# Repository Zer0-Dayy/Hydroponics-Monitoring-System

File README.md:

# Hydroponics Monitoring System

An ESP32-S3 controller monitors a hydroponic reservoir and its surroundings,
makes local grow-lamp and alarm decisions, and sends readings to a Windows or
Linux desktop app over Bluetooth Low Energy (BLE). The app handles sensor
setup, calibration, diagnostics, and history export. The custom PCB is
designed to keep the controller and selected sensors powered from a 3S
battery when external 5 V is lost.

## Start here

| If you want to… | Start with… |
| --- | --- |
| Explore without a board | [Install the desktop app](BluetoothControlApp/Readme.md#install-and-run) and [walk through the simulator](BluetoothControlApp/Readme.md#walk-through-the-demo). |
| Review or manufacture the PCB | Open the [Rev 1.5 PCB guide](PCB%20Design/README.md) for the schematic, connector pinout, power paths, BOM, and fabrication checks. |
| Build or flash firmware | [Build with PlatformIO](Firmware/README.md#build-and-test) and follow the [bench bring-up](Firmware/README.md#bench-bring-up). |
| Commission a controller | [Connect over BLE](BluetoothControlApp/Readme.md#connect-to-a-controller), then check sensor health, calibrate the probes, and export a sample history. |
| Work on the app or protocol | See the [app development guide](BluetoothControlApp/Readme.md#develop-and-test) and the [BLE v2 contract](BluetoothControlApp/FirmwareContract.md). |

## How it fits together

```mermaid
flowchart LR
    Sensors["Seven sensor modules"] --> Controller["ESP32-S3 and FreeRTOS"]
    Controller --> Relay["Grow-lamp relay control"]
    Controller <-->|BLE v2| App["Hydroponics Control desktop app"]
    App --> History["Local SQLite history"]
    Controller -->|Optional Wi-Fi| Network["Access point"]
```

The PCB routes I²C, 1-Wire, analog inputs, and ultrasonic timing signals
to the ESP32-S3. The firmware schedules measurements and publishes a
snapshot with units, sample age, and health. A separate Safety task owns
the relay, so local control continues independently of the desktop
connection. The controller stores sensor settings and calibration in
flash. The app keeps a separate copy of the readings it receives.

BLE carries live State, Telemetry, alarms, and commissioning commands.
The Wi-Fi page configures the controller's own network connection. MQTT
publishing and a remote dashboard appear in the redesign documents as
planned work. The current system uses the BLE desktop app and local
history.

## What it measures

| Sensor | Measurements | Power branch |
| --- | --- | --- |
| BME280 | Air temperature (°C), relative humidity (% RH), and pressure (Pa) | Retained 3.3 V |
| DS18B20 | Water temperature (°C) | Retained 3.3 V |
| DFR0026 | Light signal (mV), or illuminance (lux) after reference calibration | Retained 3.3 V |
| SGP30 | Total volatile organic compounds (ppb) and estimated CO₂ equivalent (ppm) | Retained 3.3 V |
| HC-SR04 | Distance to the water surface (mm) | External 5 V |
| pH-4502C | Reservoir pH | External 5 V |
| SEN0244 | Temperature-compensated total dissolved solids (ppm) | External 5 V |

The relay interface also uses external 5 V. Firmware 0.11.0 reports the
external power state by default. The optional power handover stops 5 V
sensing and pauses Wi-Fi on rail loss. That mode still needs validation
on the assembled board. The BLE link is open and carries Wi-Fi
credentials unencrypted. [Firmware power policy](Firmware/README.md#power-and-safety-policy) · [BLE link details](BluetoothControlApp/FirmwareContract.md#bluetooth-le)

## Design references and project history

- The October redesign defines the system requirements and validation
  plan. The SysML package maps requirements to components, interfaces,
  and test cases. [Redesign specification, Rev 5](Documentation/Redesign%20Specification.pdf) · [SysML diagrams](Documentation/SysML%20Diagrams.pdf)
- The firmware architecture records module boundaries and design
  decisions. Its RTOS companion explains tasks, scheduling, and
  supervision. The guided textbook walks through a snapshot of the
  implementation. [Firmware architecture](Firmware/Firmware%20Architecture.pdf) · [RTOS architecture](Firmware/RTOS%20Architecture.pdf) · [Guided firmware textbook](Documentation/Hydroponics%20Firmware.pdf)
- The dated bench notes preserve the earlier development-board and
  breadboard results. Use the Rev 1.5 schematic and connector guide when
  wiring the custom PCB. [Bench notes](Firmware/docs/bench-notes.md) · [PCB guide](PCB%20Design/README.md)
- The original handover documents the earlier ESP32, EdgeX, and MQTT
  prototype. The provenance document records the current firmware and app
  source, attribution, and license scope. [Original handover](Project%20Handover/Source%20Code/HANDOVER.md) · [Provenance](PROVENANCE.md)

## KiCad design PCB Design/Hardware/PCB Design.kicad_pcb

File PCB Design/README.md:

# Hydroponics Monitoring System · PCB revision 1.8

Open **Hardware/PCB Design.kicad_pro** in KiCad 10. The fabrication plots, assembly exports and rule checks were regenerated using **KiCad 10.0.8**. Install the standard KiCad 10 symbol libraries and the optional KiCad 10 3D model library to view the packaged model references.
 
See **Documentation/Port And LED Map.pdf** for the USB, UART and indicator locations. **BOM/Instructions Atelier.md** defines the factory assembly.

## Manufacturing handoff

| Directory | Contents |
| --- | --- |
| Hardware | Editable KiCad project, schematic, board, local symbols, footprints and library tables. Open PCB Design.kicad_pro. |
| Fabrication | 2-layer Gerbers, both silkscreens, plated and non-plated drill files with G85 slots, Gerber job and IPC-D-356 electrical test netlist. |
| BOM | Assembly_BOM.csv gives the factory population status for every schematic item. Placement_Top_SMT.csv is the default SMT pick-and-place file. Positions_All_Design.csv is a coordinate reference for all 84 footprints. Sourcing_Notes.csv retains earlier candidate suppliers and adds the Rev 1.8 components. |
| Documentation | Schematic, 1:1 top assembly and mirrored back markings, front and back copper drawings viewed from above, and the connector and LED map. |
| Validation | KiCad 10 ERC and DRC reports, drill maps, and regeneration checks for connectivity, geometry and the assembly files. |

**Factory build**. Fit the J15/J16 1×5 female through-hole sockets, the J17 1×4 male header, J18 1×2 header with removable shorting shunt and all five LEDs. Fit both Micro-B receptacles and all three 0Ω links. The front stencil includes these five parts. Solder and inspect all four shell anchors on each receptacle. Leave J9, J10 and J12 empty for the owner’s modules. Supply both silkscreens. Maintain the original 165.5 × 90.5 mm outline, four M3 mounting positions, 1.5 mm FR-4 and 35 µm copper per side. Review plated shell slots and the four new non-plated standoff slots with the fabricator.

## USB service options

| Function | Plug-in breakout | Factory-installed primary | If a port is damaged |
| --- | --- | --- | --- |
| Native data | J15. Pin 2 D−, pin 3 D+, pin 5 GND. Pins 1 and 4 isolated. | Fit a mechanically matched J1 and both 0Ω links R25/R26. | Disconnect power. Remove both links to isolate the direct D lines. Inspect the footprint for shorts to power or ground before installing a supported J15 breakout. |
| External 5V | J16. Pin 1 VBUS and pin 5 GND. Pins 2–4 isolated. | Fit a mechanically matched J3 and R27. Use a jumper rated ≥1.5A. | Disconnect power. Remove R27 to isolate J3 VBUS. Inspect for shorts and supply 5V through J16. |
| ROM recovery | J17. Pin 1 GND, pin 2 PCB TX, pin 3 PCB RX, pin 4 ESP_3V3. | 3.3V USB-to-UART adapter with crossed TX/RX and either board power (J18 closed, pin 4 free) or ESP-only power (J18 open). | The ROM can return its MAC address over UART even when the native USB path is unusable. |

Use a single host for native data and a single source for EXT_5V. With power off, desolder the indicated 0Ω component(s) and leave their copper pads intact. Verify isolation before attaching the replacement breakout. The J15 carrier and J1 occupy a common plug-access area. For a different carrier shape, secure the carrier to the enclosure and use a short pin-mapped harness. The unknown generic loose receptacle has no verified land pattern. Check the proposed part against the Amphenol footprint before assembly; flag a mismatch before fitting a substitute.

## Field connector pinout

| Ref | Terminals in numerical order | ESP32-S3 signal |
| --- | --- | --- |
| J2 · BME280 and J11 · SGP30 | SDA, SCL, GND, 3.3V | GPIO21 SDA, GPIO47 SCL |
| J4 · DS18B20 | GND, 3.3V, DQ | GPIO14 |
| J5 · SEN0244 | GND, EXT_5V, AOUT | GPIO6 |
| J7 · HC-SR04 | EXT_5V, TRIG, ECHO, GND | GPIO17 trigger, GPIO18 divided echo |
| J8 · DFR0026 | Signal, 3.3V, GND | GPIO1 |
| J13 · Relay | EXT_5V, relay control, GND | GPIO15 |
| J14 · pH-4502C | EXT_5V, GND, GND, PO | GPIO7 through divider |

J6 accepts battery positive on pin 1 and ground on pin 2. J9 produces BAT_5V. The common diode cathodes feed J12 at SYS_IN. External-rail sensing remains on GPIO8 through 10kΩ over 13.6kΩ. J5 pin 2 now reads EXT_5V in its schematic symbol. Its electrical connection is the same as Rev 1.5.

## Bench evidence

At first power-up, measure the rails to ground. D3 indicates EXT_5V, D4 indicates BAT_5V, D5 indicates SYS_IN after the isolation diodes, and D6 indicates the ESP supply at U1. D7 is active high on GPIO9 and requires firmware that toggles that output. EN should return high after reset. Enter the ROM loader for the read-only MAC test, then run a GPIO9 heartbeat application on a test board if desired. A toggling GPIO9 proves the diagnostic task is running. Qualify the sensor channels, UPS handover, USB connection under cable movement and loaded rails on a physical first article.

To repeat the CAD checks from the Hardware directory:

```sh
kicad-cli sch erc --exit-code-violations -o erc.rpt 'PCB Design.kicad_sch'
kicad-cli pcb drc --all-track-errors --schematic-parity --exit-code-violations -o drc.rpt 'PCB Design.kicad_pcb'
```

## ESP-only programming

With all power off, remove the J18 shunt and disconnect external 5V, battery, charger and sensor/relay cables. Feed regulated 3.3V rated for at least 500mA into J17 pin 4 with common ground on pin 1. Use 3.3V UART logic. Use a separate 3.3V supply if the adapter cannot supply that current. After flashing, disconnect programmer power before reinstalling the J18 shunt for normal operation. D6 indicates the local ESP rail. Before plugging in sensors, verify that J12 OUT+ and J2 pin 4 remain near 0V in this mode. Peripheral GPIOs can feed unpowered devices through their protection diodes.

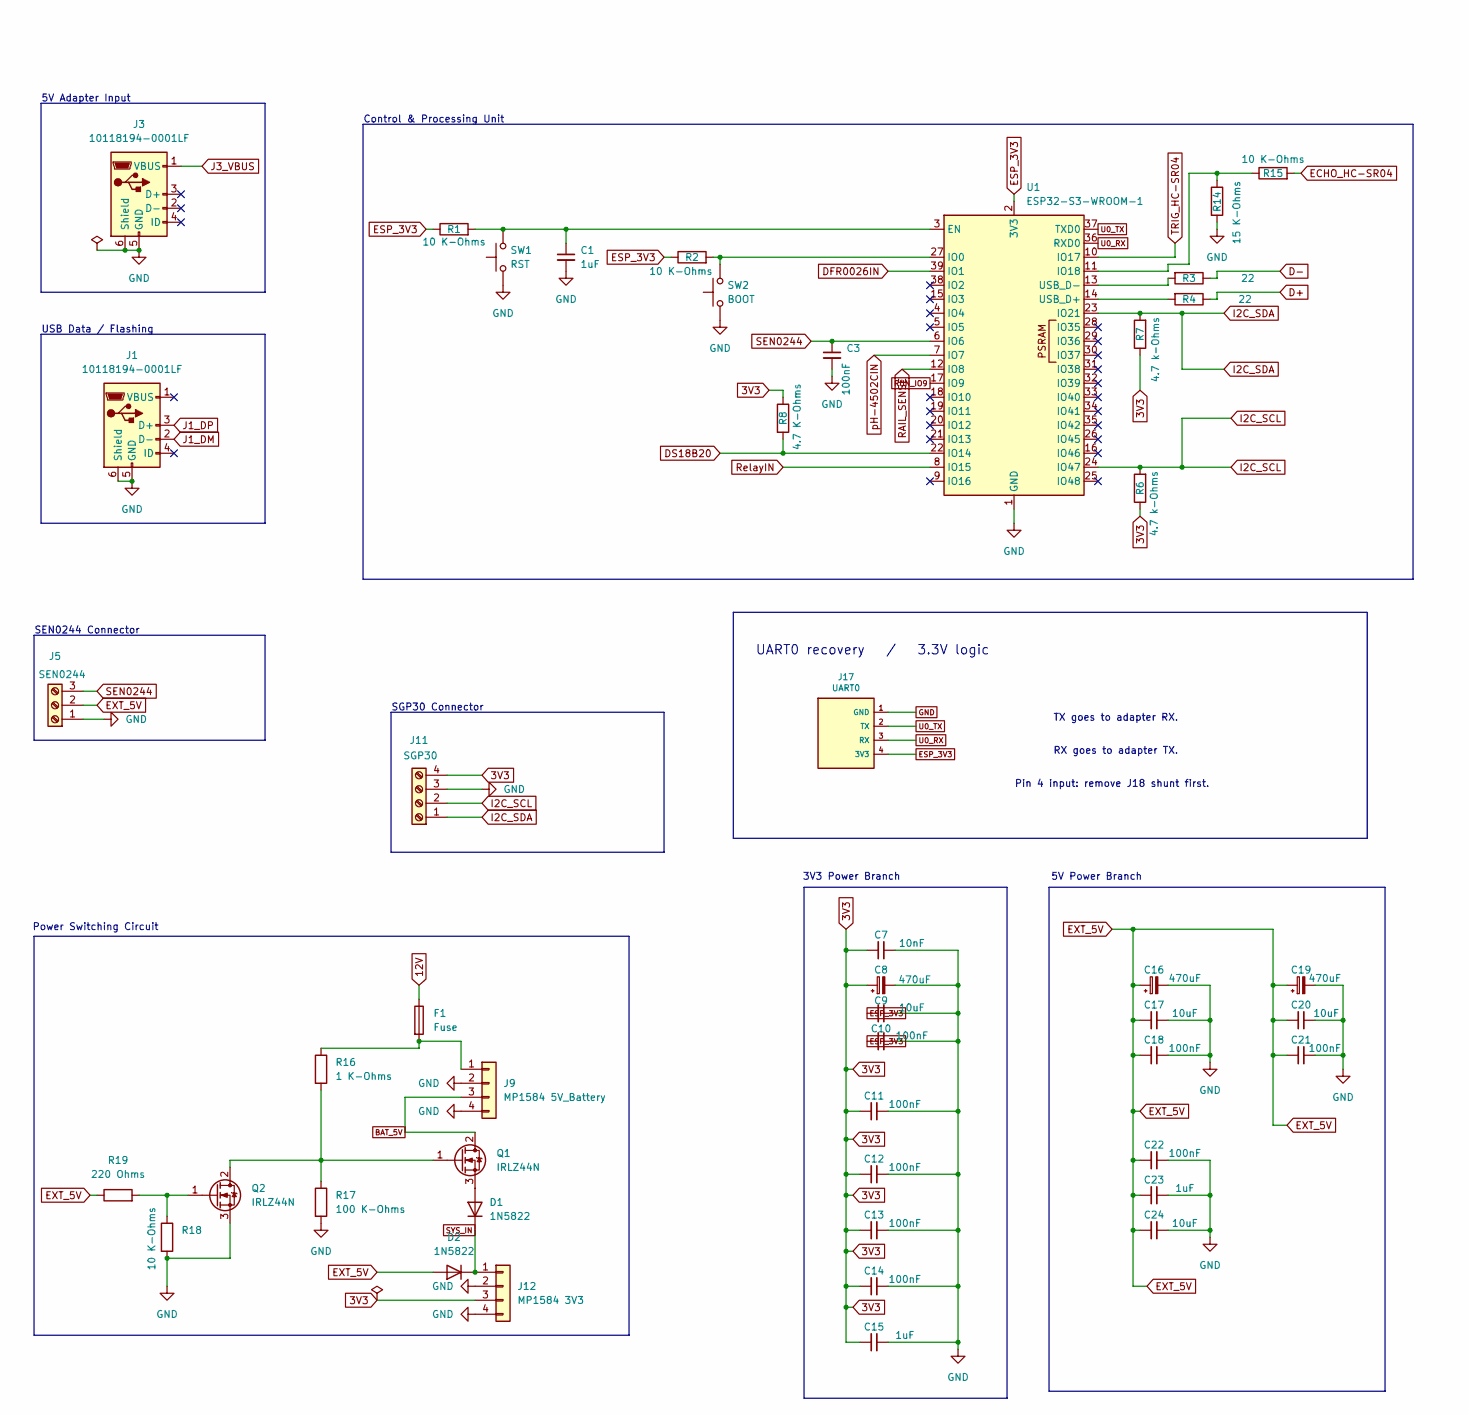
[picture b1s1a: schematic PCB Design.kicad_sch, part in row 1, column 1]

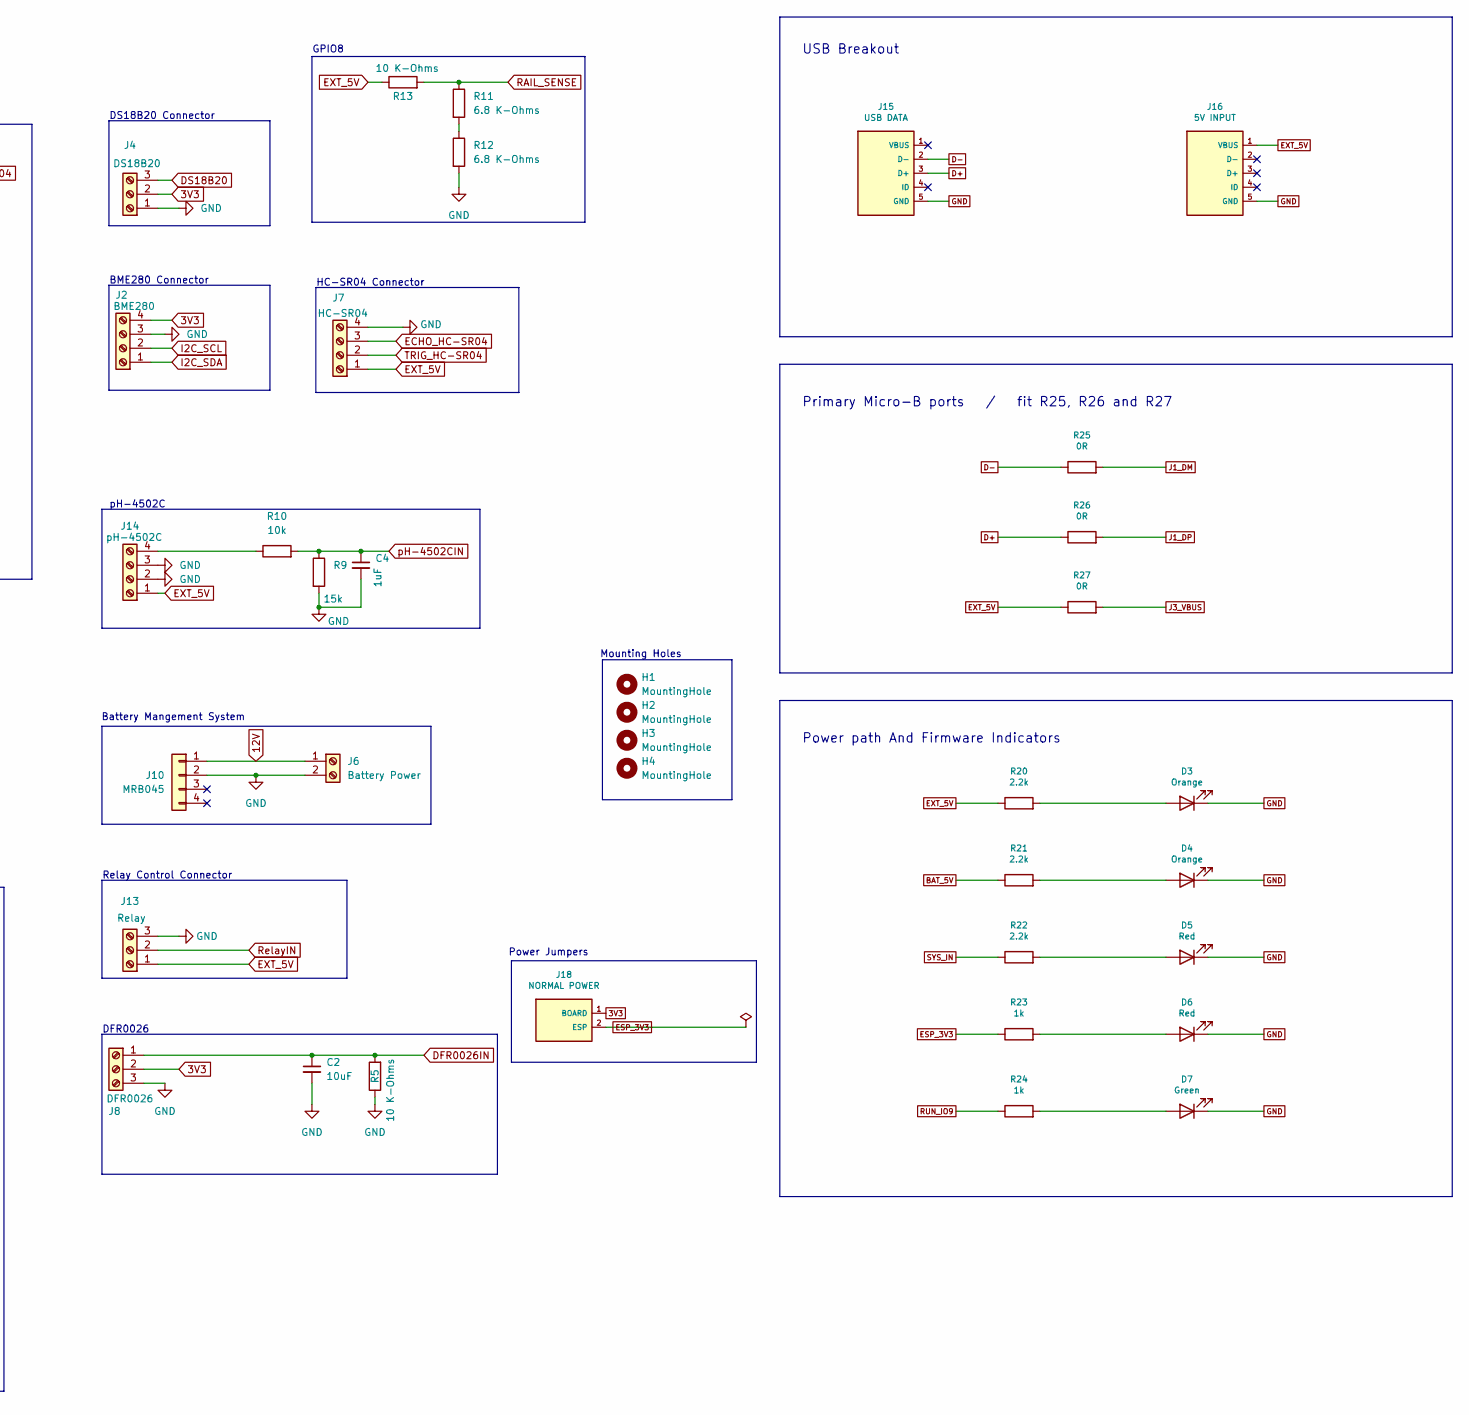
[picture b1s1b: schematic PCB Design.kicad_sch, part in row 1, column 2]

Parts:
C1: 1uF; C_0402_1005Metric__C1
C2: 10uF; C_0805_2012Metric__C2
C3: 100nF; C_0805_2012Metric_Pad1.18x1.45mm_HandSolder__C3
C4: 1uF; C_0402_1005Metric__C4
C7: 10nF; C_0805_2012Metric__C7
C8: 470uF; CP_Radial_D5.0mm_P2.00mm__C8
C9: 10uF; C_0805_2012Metric__C9
C10: 100nF; C_0805_2012Metric__C10
C11: 100nF; C_0805_2012Metric__C11
C12: 100nF; C_0805_2012Metric__C12
C13: 100nF; C_0805_2012Metric__C13
C14: 100nF; C_0805_2012Metric__C14
C15: 1uF; C_0402_1005Metric__C15
C16: 470uF; CP_Radial_D5.0mm_P2.00mm__C16
C17: 10uF; C_0805_2012Metric__C17
C18: 100nF; C_0805_2012Metric__C18
C19: 470uF; CP_Radial_D5.0mm_P2.00mm__C19
C20: 10uF; C_0805_2012Metric__C20
C21: 100nF; C_0805_2012Metric__C21
C22: 100nF; C_0805_2012Metric__C22
C23: 1uF; C_0402_1005Metric__C23
C24: 10uF; C_0805_2012Metric__C24
D1: 1N5822; D_DO-201AD_P15.24mm_Horizontal__D1
D2: 1N5822; D_DO-201AD_P15.24mm_Horizontal__D2
D3, D4: Orange; LED_1206_3216Metric
D5, D6: Red; LED_1206_3216Metric
D7: Green; LED_1206_3216Metric
F1: Fuse; Fuse_Littelfuse_395Series__F1
H1: MountingHole; MountingHole_3.2mm_M3__H1
H2: MountingHole; MountingHole_3.2mm_M3__H2
H3: MountingHole; MountingHole_3.2mm_M3__H3
H4: MountingHole; MountingHole_3.2mm_M3__H4
J1, J3: 10118194-0001LF; USB_Micro-B_Amphenol_10118194-0001LF_Horizontal
J2: BME280; TerminalBlock_Phoenix_MKDS-1,5-4-5.08_1x04_P5.08mm_Horizont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
J4: DS18B20; TerminalBlock_Phoenix_MKDS-1,5-3-5.08_1x03_P5.08mm_Horizont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
J5: SEN0244; TerminalBlock_Phoenix_MKDS-1,5-3-5.08_1x03_P5.08mm_Horizont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
J6: Battery Power; TerminalBlock_Phoenix_MKDS-1,5-2-5.08_1x02_P5.08mm_Horizont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
J7: HC-SR04; TerminalBlock_Phoenix_MKDS-1,5-4-5.08_1x04_P5.08mm_Horizont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
J8: DFR0026; TerminalBlock_Phoenix_MKDS-1,5-3-5.08_1x03_P5.08mm_Horizont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
J9: MP1584 5V_Battery; MP1584EN_Module__J9
J10: MRB045; Charger_3S_TypeC_MRB045__J10
J11: SGP30; TerminalBlock_Phoenix_MKDS-1,5-4-5.08_1x04_P5.08mm_Horizont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
J12: MP1584 3V3; MP1584EN_Module__J12
J13: Relay; TerminalBlock_Phoenix_MKDS-1,5-3-5.08_1x03_P5.08mm_Horizont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
J14: pH-4502C; TerminalBlock_Phoenix_MKDS-1,5-4-5.08_1x04_P5.08mm_Horizont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
J15: USB DATA; USB_Breakout_1x05_M2
J16: 5V INPUT; USB_Breakout_1x05_M2
J17: UART0; PinHeader_1x04_P2.54mm_Vertical
J18: NORMAL POWER; PinHeader_1x02_P2.54mm_Vertical
Q1: IRLZ44N; TO-220-3_Vertical__Q1
Q2: IRLZ44N; TO-220-3_Vertical__Q2
R1: 10 K-Ohms; R_0603_1608Metric__R1
R2: 10 K-Ohms; R_0603_1608Metric__R2
R3: 22; R_0603_1608Metric__R3
R4: 22; R_0603_1608Metric__R4
R5: 10 K-Ohms; R_0603_1608Metric__R5
R6: 4.7 k-Ohms; R_0603_1608Metric__R6
R7: 4.7 k-Ohms; R_0603_1608Metric__R7
R8: 4.7 K-Ohms; R_0603_1608Metric__R8
R9: 15k; R_0603_1608Metric__R9
R10: 10k; R_0603_1608Metric__R10
R11: 6.8 K-Ohms; R_0603_1608Metric__R11; Tolerance 1%
R12: 6.8 K-Ohms; R_0603_1608Metric__R12; Tolerance 1%
R13: 10 K-Ohms; R_0603_1608Metric__R13; Tolerance 1%
R14: 15 K-Ohms; R_0603_1608Metric__R14; Tolerance 1%
R15: 10 K-Ohms; R_0603_1608Metric__R15; Tolerance 1%
R16: 1 K-Ohms; R_1206_3216Metric__R16
R17: 100 K-Ohms; R_0603_1608Metric__R17
R18: 10 K-Ohms; R_0603_1608Metric__R18
R19: 220 Ohms; R_0603_1608Metric__R19
R20, R21, R22: 2.2k; R_1206_3216Metric
R23, R24: 1k; R_1206_3216Metric
R25, R26: 0R; R_0603_1608Metric
R27: 0R; R_1206_3216Metric_HandLink
SW1: RST; SW_PUSH_6mm_H7.3mm__SW1
SW2: BOOT; SW_PUSH_6mm_H7.3mm__SW2
U1: ESP32-S3-WROOM-1; ESP32-S3-WROOM-1__U1

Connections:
3V3: C7.1, C8.1, C11.1, C12.1, C13.1, C14.1, C15.1, J2.4 (3V3), J4.2 (3V3), J8.2 (3V3), J11.4 (3V3), J12.3 (OUT+), J18.1 (BOARD), R6.1, R7.1, R8.1
12V: F1.1, J6.1, J10.1 (BAT+)
BAT_5V: J9.3 (OUT+), Q1.2 (D), R21.1
D+: J15.3 (D+), R4.1, R26.1
D-: J15.2 (D-), R3.1, R25.1
DFR0026IN: C2.1, J8.1 (SIGNAL), R5.2, U1.39 (IO1)
DS18B20: J4.3 (DQ), R8.2, U1.22 (IO14)
ECHO_HC-SR04: J7.3 (ECHO), R15.2
ESP_3V3: C9.1, C10.1, J17.4 (3V3), J18.2 (ESP), R1.1, R2.1, R23.1, U1.2 (3V3)
EXT_5V: C16.1, C17.1, C18.1, C19.1, C20.1, C21.1, C22.1, C23.1, C24.1, D2.2 (A), J5.2 (EXT_5V), J7.1 (5V), J13.1 (EXT_5V), J14.1 (EXT_5V), J16.1 (VBUS), R13.1, R19.1, R20.1, R27.1
GND: C1.2, C2.2, C3.2, C4.2, C7.2, C8.2, C9.2, C10.2, C11.2, C12.2, C13.2, C14.2, C15.2, C16.2, C17.2, C18.2, C19.2, C20.2, C21.2, C22.2, C23.2, C24.2, D3.1 (K), D4.1 (K), D5.1 (K), D6.1 (K), D7.1 (K), J1.5 (GND), J1.6 (Shield), J2.3 (GND), J3.5 (GND), J3.6 (Shield), J4.1 (GND), J5.1 (GND), J6.2, J7.4 (GND), J8.3 (GND), J9.2 (IN-), J9.4 (OUT-), J10.2 (BAT-), J11.3 (GND), J12.2 (IN-), J12.4 (OUT-), J13.3 (GND), J14.2 (GND), J14.3 (GND), J15.5 (GND), J16.5 (GND), J17.1 (GND), Q2.3 (S), R5.1, R9.2, R12.2, R14.2, R17.2, R18.2, SW1.1, SW2.1, U1.1 (GND), U1.40 (GND), U1.41 (GND)
I2C_SCL: J2.2 (SCL), J11.2 (SCL), R6.2, U1.24 (IO47)
I2C_SDA: J2.1 (SDA), J11.1 (SDA), R7.2, U1.23 (IO21)
J1_DM: J1.2 (D-), R25.2
J1_DP: J1.3 (D+), R26.2
J3_VBUS: J3.1 (VBUS), R27.2
unnamed: D1.2 (A), Q1.3 (S)
unnamed: D3.2 (A), R20.2
unnamed: D4.2 (A), R21.2
unnamed: D5.2 (A), R22.2
unnamed: D6.2 (A), R23.2
unnamed: D7.2 (A), R24.2
unnamed: F1.2, J9.1 (IN+), R16.1
unnamed: J14.4 (PO_ANALOG), R10.1
unnamed: Q1.1 (G), Q2.2 (D), R16.2, R17.1
unnamed: Q2.1 (G), R18.1, R19.2
unnamed: R11.2, R12.1
unnamed: C1.1, R1.2, SW1.2, U1.3 (EN)
unnamed: R2.2, SW2.2, U1.27 (IO0)
unnamed: R14.1, R15.1, U1.11 (IO18)
unnamed: R4.2, U1.14 (USB_D+)
unnamed: R3.2, U1.13 (USB_D-)
RAIL_SENSE: R11.1, R13.2, U1.12 (IO8)
RUN_IO9: R24.1, U1.17 (IO9)
RelayIN: J13.2 (RELAY_CTRL), U1.8 (IO15)
SEN0244: C3.1, J5.3 (AOUT), U1.6 (IO6)
SYS_IN: D1.1 (K), D2.1 (K), J12.1 (IN+), R22.1
TRIG_HC-SR04: J7.2 (TRIG), U1.10 (IO17)
U0_RX: J17.3 (RX), U1.36 (RXD0)
U0_TX: J17.2 (TX), U1.37 (TXD0)
pH-4502CIN: C4.1, R9.1, R10.2, U1.7 (IO7)

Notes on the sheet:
RX goes to adapter TX.
Control & Processing Unit
SEN0244 Connector
Primary Micro-B ports / fit R25, R26 and R27
USB Breakout
HC-SR04 Connector
3V3 Power Branch
SGP30 Connector
Power Switching Circuit
Power Jumpers
Mounting Holes
DFR0026
pH-4502C
BME280 Connector
UART0 recovery / 3.3V logic
Battery Mangement System
GPIO8
Pin 4 input: remove J18 shunt first.
Relay Control Connector
DS18B20 Connector
TX goes to adapter RX.
5V Power Branch
Power path And Firmware Indicators
USB Data / Flashing
5V Adapter Input

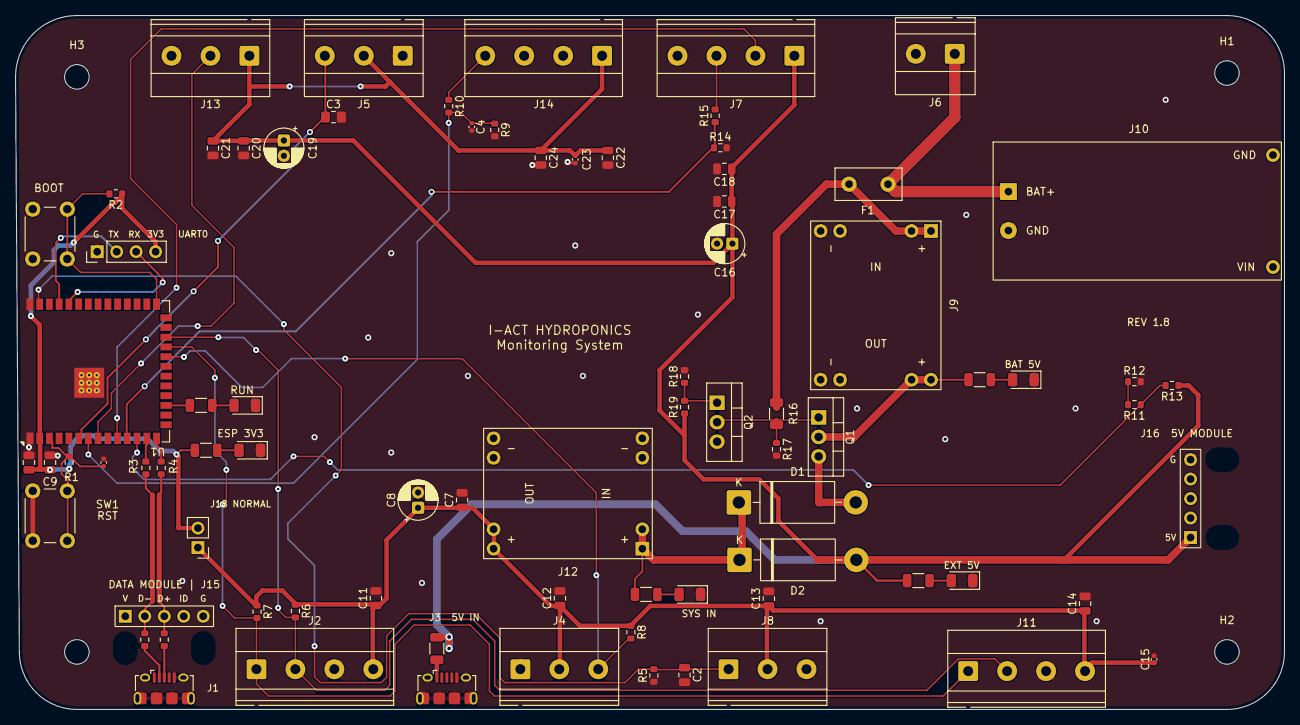
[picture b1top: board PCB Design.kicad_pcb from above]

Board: 2 copper layers, 165.5 x 90.5 mm, 84 parts (0 on the bottom side), 41 nets.

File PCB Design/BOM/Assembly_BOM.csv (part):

Ref,Quantity,Value,Footprint,Breakout build,Assembly note
C1,1,1uF,ProjectPCB:C_0402_1005Metric__C1,Fit — SMT,See footprint and sourcing notes.
C2,1,10uF,ProjectPCB:C_0805_2012Metric__C2,Fit — SMT,See footprint and sourcing notes.
C3,1,100nF,ProjectPCB:C_0805_2012Metric_Pad1.18x1.45mm_HandSolder__C3,Fit — SMT,See footprint and sourcing notes.
C4,1,1uF,ProjectPCB:C_0402_1005Metric__C4,Fit — SMT,See footprint and sourcing notes.
C7,1,10nF,ProjectPCB:C_0805_2012Metric__C7,Fit — SMT,See footprint and sourcing notes.
C8,1,470uF,ProjectPCB:CP_Radial_D5.0mm_P2.00mm__C8,Fit — hand assembly,"470uF radial; 5 mm diameter, 2 mm lead pitch. Verify voltage rating and body fit against board before assembly."
C9,1,10uF,ProjectPCB:C_0805_2012Metric__C9,Fit — SMT,See footprint and sourcing notes.
C10,1,100nF,ProjectPCB:C_0805_2012Metric__C10,Fit — SMT,See footprint and sourcing notes.
C11,1,100nF,ProjectPCB:C_0805_2012Metric__C11,Fit — SMT,See footprint and sourcing notes.
C12,1,100nF,ProjectPCB:C_0805_2012Metric__C12,Fit — SMT,See footprint and sourcing notes.
C13,1,100nF,ProjectPCB:C_0805_2012Metric__C13,Fit — SMT,See footprint and sourcing notes.
C14,1,100nF,ProjectPCB:C_0805_2012Metric__C14,Fit — SMT,See footprint and sourcing notes.
C15,1,1uF,ProjectPCB:C_0402_1005Metric__C15,Fit — SMT,See footprint and sourcing notes.
C16,1,470uF,ProjectPCB:CP_Radial_D5.0mm_P2.00mm__C16,Fit — hand assembly,"470uF radial; 5 mm diameter, 2 mm lead pitch. Verify voltage rating and body fit against board before assembly."
C17,1,10uF,ProjectPCB:C_0805_2012Metric__C17,Fit — SMT,See footprint and sourcing notes.
C18,1,100nF,ProjectPCB:C_0805_2012Metric__C18,Fit — SMT,See footprint and sourcing notes.
C19,1,470uF,ProjectPCB:CP_Radial_D5.0mm_P2.00mm__C19,Fit — hand assembly,"470uF radial; 5 mm diameter, 2 mm lead pitch. Verify voltage rating and body fit against board before assembly."
C20,1,10uF,ProjectPCB:C_0805_2012Metric__C20,Fit — SMT,See footprint and sourcing notes.
C21,1,100nF,ProjectPCB:C_0805_2012Metric__C21,Fit — SMT,See footprint and sourcing notes.
C22,1,100nF,ProjectPCB:C_0805_2012Metric__C22,Fit — SMT,See footprint and sourcing notes.
C23,1,1uF,ProjectPCB:C_0402_1005Metric__C23,Fit — SMT,See footprint and sourcing notes.
C24,1,10uF,ProjectPCB:C_0805_2012Metric__C24,Fit — SMT,See footprint and sourcing notes.
D1,1,1N5822,ProjectPCB:D_DO-201AD_P15.24mm_Horizontal__D1,Fit — hand assembly,See footprint and sourcing notes.
D2,1,1N5822,ProjectPCB:D_DO-201AD_P15.24mm_Horizontal__D2,Fit — hand assembly,See footprint and sourcing notes.
D3,1,Orange,ProjectPCB:LED_1206_3216Metric,Fit — SMT,"1206 LED, pad 1 cathode. Low-current indicator; select green with Vf at most 2.3V near 1mA for D7."
D4,1,Orange,ProjectPCB:LED_1206_3216Metric,Fit — SMT,"1206 LED, pad 1 cathode. Low-current indicator; select green with Vf at most 2.3V near 1mA for D7."
D5,1,Red,ProjectPCB:LED_1206_3216Metric,Fit — SMT,"1206 LED, pad 1 cathode. Low-current indicator; select green with Vf at most 2.3V near 1mA for D7."
D6,1,Red,ProjectPCB:LED_1206_3216Metric,Fit — SMT,"1206 LED, pad 1 cathode. Low-current indicator; select green with Vf at most 2.3V near 1mA for D7."
D7,1,Green,ProjectPCB:LED_1206_3216Metric,Fit — SMT,"1206 LED, pad 1 cathode. Low-current indicator; select green with Vf at most 2.3V near 1mA for D7."
F1,1,Fuse,ProjectPCB:Fuse_Littelfuse_395Series__F1,Fit — hand assembly,See footprint and sourcing notes.
J1,1,10118194-0001LF,ProjectPCB:USB_Micro-B_Amphenol_10118194-0001LF_Horizontal,Fit — SMT,Primary USB data; Amphenol 10118194-0001LF or verified match. Solder all 4 anchors.
J2,1,BME280,"ProjectPCB:TerminalBlock_Phoenix_MKDS-1,5-4-5.08_1x04_P5.08mm_Horizontal__J2",Fit — hand assembly,See footprint and sourcing notes.
J3,1,10118194-0001LF,ProjectPCB:USB_Micro-B_Amphenol_10118194-0001LF_Horizontal,Fit — SMT,Primary 5V input; Amphenol 10118194-0001LF or verified match. Solder all 4 anchors.
J4,1,DS18B20,"ProjectPCB:TerminalBlock_Phoenix_MKDS-1,5-3-5.08_1x03_P5.08mm_Horizontal__J4",Fit — hand assembly,See footprint and sourcing notes.
J5,1,SEN0244,"ProjectPCB:TerminalBlock_Phoenix_MKDS-1,5-3-5.08_1x03_P5.08mm_Horizontal__J5",Fit — hand assembly,See footprint and sourcing notes.
J6,1,Battery Power,"ProjectPCB:TerminalBlock_Phoenix_MKDS-1,5-2-5.08_1x02_P5.08mm_Horizontal__J6",Fit — hand assembly,See footprint and sourcing notes.
J7,1,HC-SR04,"ProjectPCB:TerminalBlock_Phoenix_MKDS-1,5-4-5.08_1x04_P5.08mm_Horizontal__J7",Fit — hand assembly,See footprint and sourcing notes.
J8,1,DFR0026,"ProjectPCB:TerminalBlock_Phoenix_MKDS-1,5-3-5.08_1x03_P5.08mm_Horizontal__J8",Fit — hand assembly,See footprint and sourcing notes.
J9,1,MP1584 5V_Battery,ProjectPCB:MP1584EN_Module__J9,Owner installs,"Leave module and holes free for owner. Check pin labels, orientation and regulator setting before installing."
J10,1,MRB045,ProjectPCB:Charger_3S_TypeC_MRB045__J10,Owner installs,"Leave module and holes free for owner. Check pin labels, orientation and regulator setting before installing."
J11,1,SGP30,"ProjectPCB:TerminalBlock_Phoenix_MKDS-1,5-4-5.08_1x04_P5.08mm_Horizontal__J11",Fit — hand assembly,See footprint and sourcing notes.
J12,1,MP1584 3V3,ProjectPCB:MP1584EN_Module__J12,Owner installs,"Leave module and holes free for owner. Check pin labels, orientation and regulator setting before installing."
J13,1,Relay,"ProjectPCB:TerminalBlock_Phoenix_MKDS-1,5-3-5.08_1x03_P5.08mm_Horizontal__J13",Fit — hand assembly,See footprint and sourcing notes.
J14,1,pH-4502C,"ProjectPCB:TerminalBlock_Phoenix_MKDS-1,5-4-5.08_1x04_P5.08mm_Horizontal__J14",Fit — hand assembly,See footprint and sourcing notes.
J15,1,USB DATA,ProjectPCB:USB_Breakout_1x05_M2,Fit — hand assembly,"Straight 1x5 female socket, 2.54 mm, for 0.64 mm square posts; 1.0 mm finished holes. For J16 select contacts rated at least 1.5A."
J16,1,5V INPUT,ProjectPCB:USB_Breakout_1x05_M2,Fit — hand assembly,"Straight 1x5 female socket, 2.54 mm, for 0.64 mm square posts; 1.0 mm finished holes. For J16 select contacts rated at least 1.5A."
J17,1,UART0,ProjectPCB:PinHeader_1x04_P2.54mm_Vertical,Fit — hand assembly,"Straight 1x4 breakaway male header, 2.54 mm; pin 1 GND, pin 2 PCB TX, pin 3 PCB RX, pin 4 ESP_3V3."
J18,1,NORMAL POWER,ProjectPCB:PinHeader_1x02_P2.54mm_Vertical,Fit — hand assembly,1x2 male 2.54 mm header plus removable shunt rated at least 1A. Ship closed.
Q1,1,IRLZ44N,ProjectPCB:TO-220-3_Vertical__Q1,Fit — hand assembly,See footprint and sourcing notes.
Q2,1,IRLZ44N,ProjectPCB:TO-220-3_Vertical__Q2,Fit — hand assembly,See footprint and sourcing notes.
R1,1,10 K-Ohms,ProjectPCB:R_0603_1608Metric__R1,Fit — SMT,See footprint and sourcing notes.
R2,1,10 K-Ohms,ProjectPCB:R_0603_1608Metric__R2,Fit — SMT,See footprint and sourcing notes.
R3,1,22,ProjectPCB:R_0603_1608Metric__R3,Fit — SMT,See footprint and sourcing notes.
R4,1,22,ProjectPCB:R_0603_1608Metric__R4,Fit — SMT,See footprint and sourcing notes.
R5,1,10 K-Ohms,ProjectPCB:R_0603_1608Metric__R5,Fit — SMT,See footprint and sourcing notes.
R6,1,4.7 k-Ohms,ProjectPCB:R_0603_1608Metric__R6,Fit — SMT,See footprint and sourcing notes.
R7,1,4.7 k-Ohms,ProjectPCB:R_0603_1608Metric__R7,Fit — SMT,See footprint and sourcing notes.
R8,1,4.7 K-Ohms,ProjectPCB:R_0603_1608Metric__R8,Fit — SMT,See footprint and sourcing notes.
R9,1,15k,ProjectPCB:R_0603_1608Metric__R9,Fit — SMT,See footprint and sourcing notes.
R10,1,10k,ProjectPCB:R_0603_1608Metric__R10,Fit — SMT,See footprint and sourcing notes.
R11,1,6.8 K-Ohms,ProjectPCB:R_0603_1608Metric__R11,Fit — SMT,1% divider resistor.
R12,1,6.8 K-Ohms,ProjectPCB:R_0603_1608Metric__R12,Fit — SMT,1% divider resistor.
R13,1,10 K-Ohms,ProjectPCB:R_0603_1608Metric__R13,Fit — SMT,1% divider resistor.
R14,1,15 K-Ohms,ProjectPCB:R_0603_1608Metric__R14,Fit — SMT,1% divider resistor.
R15,1,10 K-Ohms,ProjectPCB:R_0603_1608Metric__R15,Fit — SMT,1% divider resistor.
R16,1,1 K-Ohms,ProjectPCB:R_1206_3216Metric__R16,Fit — SMT,"1k ohm 1206, at least 0.25W."
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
